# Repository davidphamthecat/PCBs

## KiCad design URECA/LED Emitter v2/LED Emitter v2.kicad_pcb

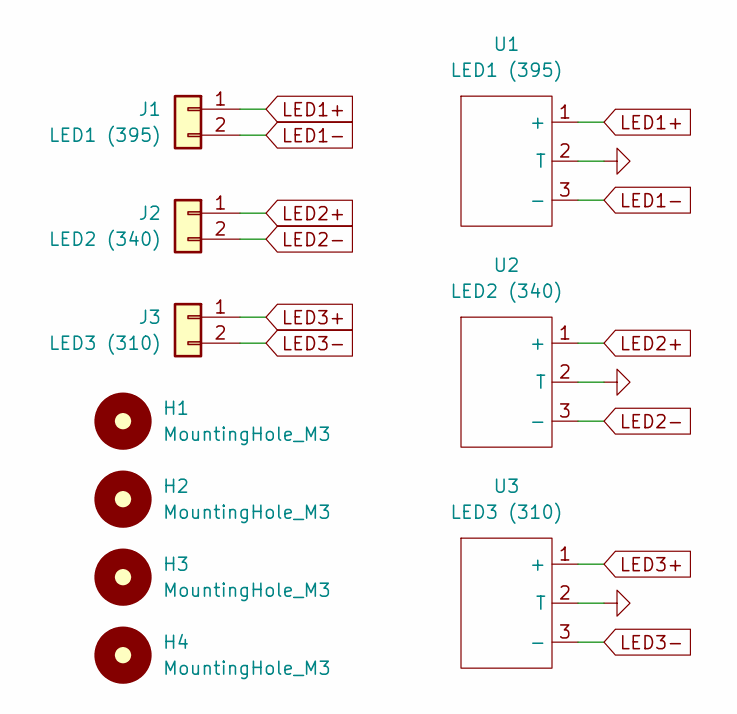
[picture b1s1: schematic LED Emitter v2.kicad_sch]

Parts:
H1, H2, H3, H4: MountingHole_M3; MountingHole_3.2mm_M3_DIN965_Pad_TopBottom; LCSC DNP
J1: LED1 (395); JST_XH_S2B-XH-A_1x02_P2.50mm_Horizontal
J2: LED2 (340); JST_XH_S2B-XH-A_1x02_P2.50mm_Horizontal
J3: LED3 (310); JST_XH_S2B-XH-A_1x02_P2.50mm_Horizontal
U1: LED1 (395); HOUKEM_LED
U2: LED2 (340); VS5252 LED
U3: LED3 (310); VS5252 LED

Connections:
GND: U1.2 (T), U2.2 (T), U3.2 (T)
LED1+: J1.1, U1.1 (+)
LED1-: J1.2, U1.3 (-)
LED2+: J2.1, U2.1 (+)
LED2-: J2.2, U2.3 (-)
LED3+: J3.1, U3.1 (+)
LED3-: J3.2, U3.3 (-)

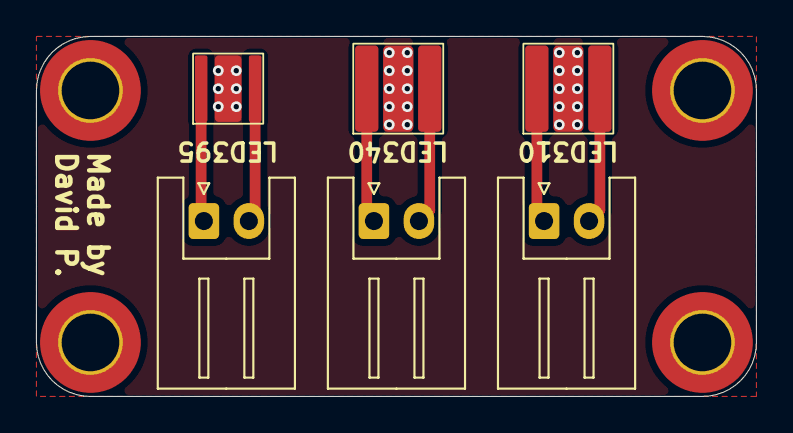
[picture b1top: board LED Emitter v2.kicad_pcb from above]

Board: 2 copper layers, 40.0 x 20.0 mm, 10 parts (0 on the bottom side), 7 nets.

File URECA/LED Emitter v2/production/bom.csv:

Designator,Footprint,Quantity,Value,LCSC Part #
"H1, H2, H3, H4",MountingHole_3.2mm_M3_DIN965_Pad_TopBottom,4,MountingHole_M3,DNP
J1,JST_XH_S2B-XH-A_1x02_P2.50mm_Horizontal,1,LED1 (395),
J2,JST_XH_S2B-XH-A_1x02_P2.50mm_Horizontal,1,LED2 (340),
J3,JST_XH_S2B-XH-A_1x02_P2.50mm_Horizontal,1,LED3 (310),
U1,HOUKEM_LED,1,LED1 (395),
U2,VS5252 LED,1,LED2 (340),
U3,VS5252 LED,1,LED3 (310),

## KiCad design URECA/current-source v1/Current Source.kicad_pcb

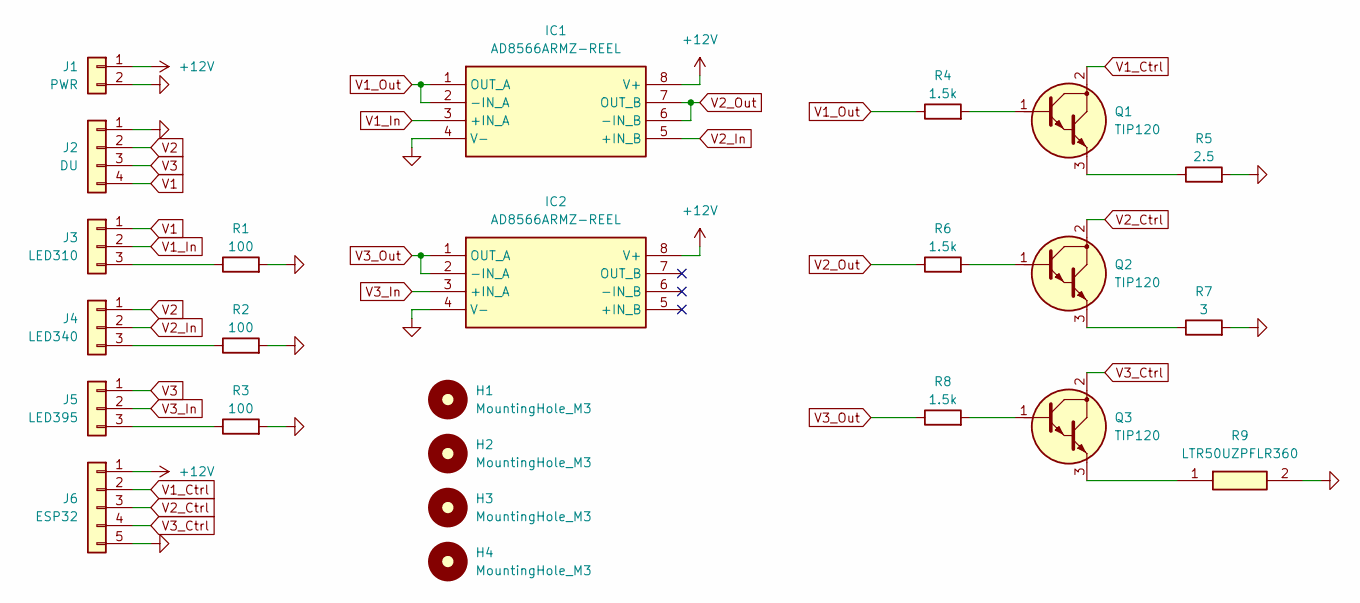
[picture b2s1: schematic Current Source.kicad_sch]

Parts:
H1, H2, H3, H4: MountingHole_M3; MountingHole_3.2mm_M3_DIN965_Pad_TopBottom; LCSC DNP
IC1, IC2: AD8566ARMZ-REEL; SOP65P490X110-8N; Mouser Part Number 584-AD8566ARMZ-R
J1: PWR; PinHeader_1x02_P1.00mm_Vertical
J2: DU; PinHeader_1x04_P1.00mm_Vertical
J3: LED310; PinHeader_1x03_P1.00mm_Vertical
J4: LED340; PinHeader_1x03_P1.00mm_Vertical
J5: LED395; PinHeader_1x03_P1.00mm_Vertical
J6: ESP32; PinHeader_1x05_P1.00mm_Vertical
Q1, Q2, Q3: TIP120; TO-220-3_Vertical_BCE
R1, R2, R3: 100; R_0805_2012Metric
R4, R6, R8: 1.5k; R_0805_2012Metric
R5: 2.5; R_1206_3216Metric
R7: 3; R_2010_5025Metric
R9: LTR50UZPFLR360; RESC2550X73N; Mouser Part Number 755-LTR50UZPFLR360

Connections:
+12V: IC1.8 (V+), IC2.8 (V+), J1.1, J6.1
GND: IC1.4 (V-), IC2.4 (V-), J1.2, J2.1, J6.5, R1.2, R2.2, R3.2, R5.2, R7.2, R9.2
unnamed: J3.3, R1.1
unnamed: J4.3, R2.1
unnamed: J5.3, R3.1
unnamed: Q1.1 (B), R4.2
unnamed: Q1.3 (E), R5.1
unnamed: Q2.1 (B), R6.2
unnamed: Q2.3 (E), R7.1
unnamed: Q3.1 (B), R8.2
unnamed: Q3.3 (E), R9.1
V1: J2.4, J3.1
V1_Ctrl: J6.2, Q1.2 (C)
V1_In: IC1.3 (+IN_A), J3.2
V1_Out: IC1.1 (OUT_A), IC1.2 (-IN_A), R4.1
V2: J2.2, J4.1
V2_Ctrl: J6.3, Q2.2 (C)
V2_In: IC1.5 (+IN_B), J4.2
V2_Out: IC1.6 (-IN_B), IC1.7 (OUT_B), R6.1
V3: J2.3, J5.1
V3_Ctrl: J6.4, Q3.2 (C)
V3_In: IC2.3 (+IN_A), J5.2
V3_Out: IC2.1 (OUT_A), IC2.2 (-IN_A), R8.1

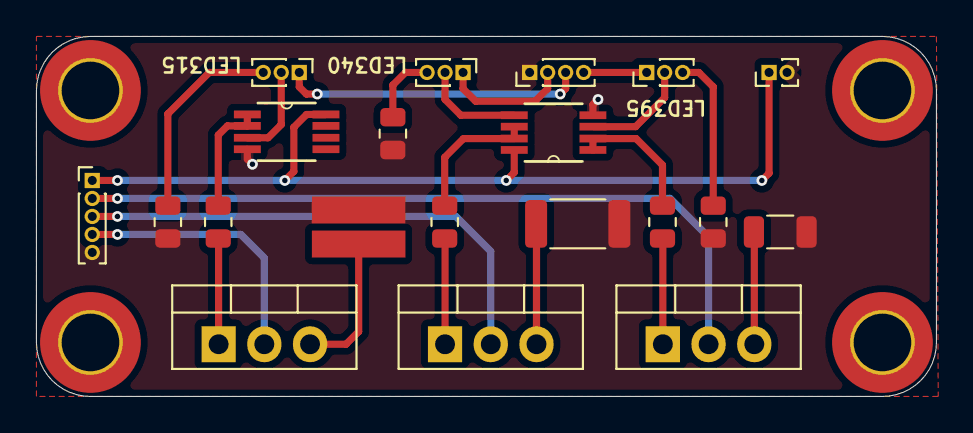
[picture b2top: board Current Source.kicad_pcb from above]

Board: 2 copper layers, 50.0 x 20.0 mm, 24 parts (0 on the bottom side), 23 nets.

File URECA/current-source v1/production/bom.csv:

Designator,Footprint,Quantity,Value,LCSC Part #
"H1, H2, H3, H4",MountingHole_3.2mm_M3_DIN965_Pad_TopBottom,4,MountingHole_M3,DNP
"IC1, IC2",SOP65P490X110-8N,2,AD8566ARMZ-REEL,
J1,PinHeader_1x02_P1.00mm_Vertical,1,PWR,
J2,PinHeader_1x04_P1.00mm_Vertical,1,DU,
J3,PinHeader_1x03_P1.00mm_Vertical,1,LED310,
J4,PinHeader_1x03_P1.00mm_Vertical,1,LED340,
J5,PinHeader_1x03_P1.00mm_Vertical,1,LED395,
J6,PinHeader_1x05_P1.00mm_Vertical,1,ESP32,
"Q1, Q2, Q3",TO-220-3_Vertical_BCE,3,TIP120,
"R1, R2, R3",0805,3,100,
"R4, R6, R8",0805,3,1.5k,
R5,1206,1,2.5,
R7,2010,1,3,
R9,RESC2550X73N,1,LTR50UZPFLR360,

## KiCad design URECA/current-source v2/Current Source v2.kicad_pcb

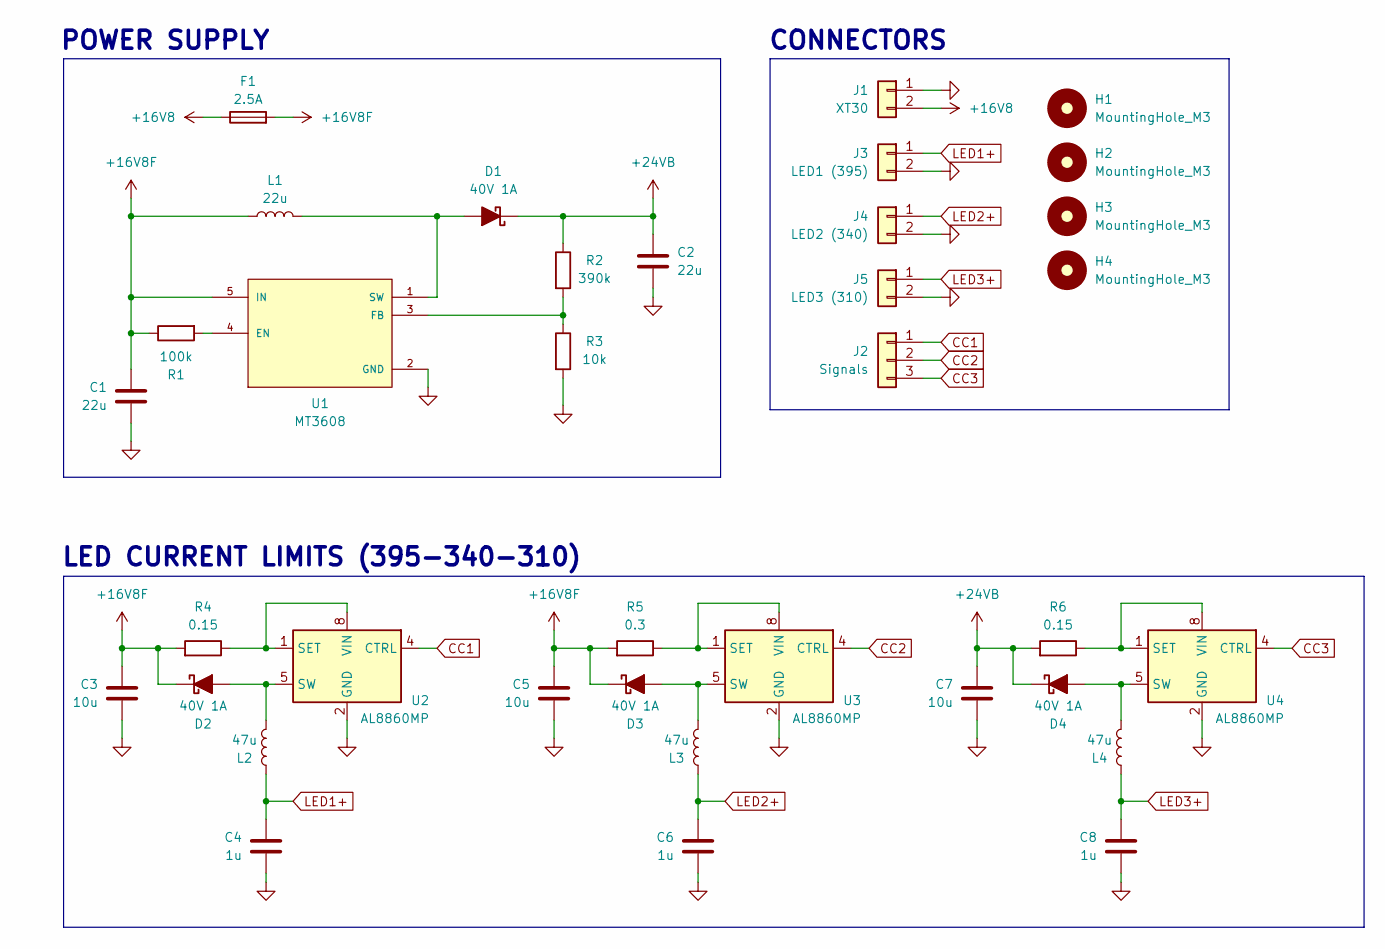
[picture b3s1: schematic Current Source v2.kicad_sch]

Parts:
C1, C2: 22u; C_0805_2012Metric
C3, C5, C7: 10u; C_0805_2012Metric
C4, C6, C8: 1u; C_0805_2012Metric
D1, D2, D3, D4: 40V 1A; D_SMA
F1: 2.5A; Fuse_1206_3216Metric
H1, H2, H3, H4: MountingHole_M3; MountingHole_3.2mm_M3_DIN965_Pad_TopBottom; LCSC DNP
J1: XT30; AMASS_XT30U-M_1x02_P5.0mm_Vertical
J2: Signals; PinHeader_1x03_P1.00mm_Vertical
J3: LED1 (395); JST_XH_B2B-XH-A_1x02_P2.50mm_Vertical
J4: LED2 (340); JST_XH_B2B-XH-A_1x02_P2.50mm_Vertical
J5: LED3 (310); JST_XH_B2B-XH-A_1x02_P2.50mm_Vertical
L1: 22u; IND_MSS7341-223MLD
L2, L3, L4: 47u; 46473C
R1: 100k; R_0805_2012Metric
R2: 390k; R_0805_2012Metric
R3: 10k; R_0805_2012Metric
R4, R6: 0.15; R_1206_3216Metric
R5: 0.3; R_1206_3216Metric
U1: MT3608; SOT95P280X145-6N; PARTREV 1.0
U2, U3, U4: AL8860MP; MSOP-8-1EP_3x3mm_P0.65mm_EP1.5x1.8mm

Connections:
+16V8: F1.1, J1.2
+16V8F: C1.1, C3.1, C5.1, D2.1 (K), D3.1 (K), F1.2, L1.1, R1.1, R4.2, R5.2, U1.5 (IN)
+24VB: C2.1, C7.1, D1.1 (K), D4.1 (K), R2.1, R6.2
CC1: J2.1, U2.4 (CTRL)
CC2: J2.2, U3.4 (CTRL)
CC3: J2.3, U4.4 (CTRL)
GND: C1.2, C2.2, C3.2, C4.2, C5.2, C6.2, C7.2, C8.2, J1.1, J3.2, J4.2, J5.2, R3.2, U1.2 (GND), U2.2 (GND), U2.3 (GND), U2.9 (GND), U3.2 (GND), U3.3 (GND), U3.9 (GND), U4.2 (GND), U4.3 (GND), U4.9 (GND)
LED1+: C4.1, J3.1, L2.1
LED2+: C6.1, J4.1, L3.1
LED3+: C8.1, J5.1, L4.1
unnamed: D1.2 (A), L1.2, U1.1 (SW)
unnamed: D2.2 (A), L2.2, U2.5 (SW), U2.6 (SW)
unnamed: D3.2 (A), L3.2, U3.5 (SW), U3.6 (SW)
unnamed: D4.2 (A), L4.2, U4.5 (SW), U4.6 (SW)
unnamed: R1.2, U1.4 (EN)
unnamed: R2.2, R3.1, U1.3 (FB)
unnamed: R4.1, U2.1 (SET), U2.8 (VIN)
unnamed: R5.1, U3.1 (SET), U3.8 (VIN)
unnamed: R6.1, U4.1 (SET), U4.8 (VIN)

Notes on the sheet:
LED CURRENT LIMITS (395-340-310)
CONNECTORS
POWER SUPPLY

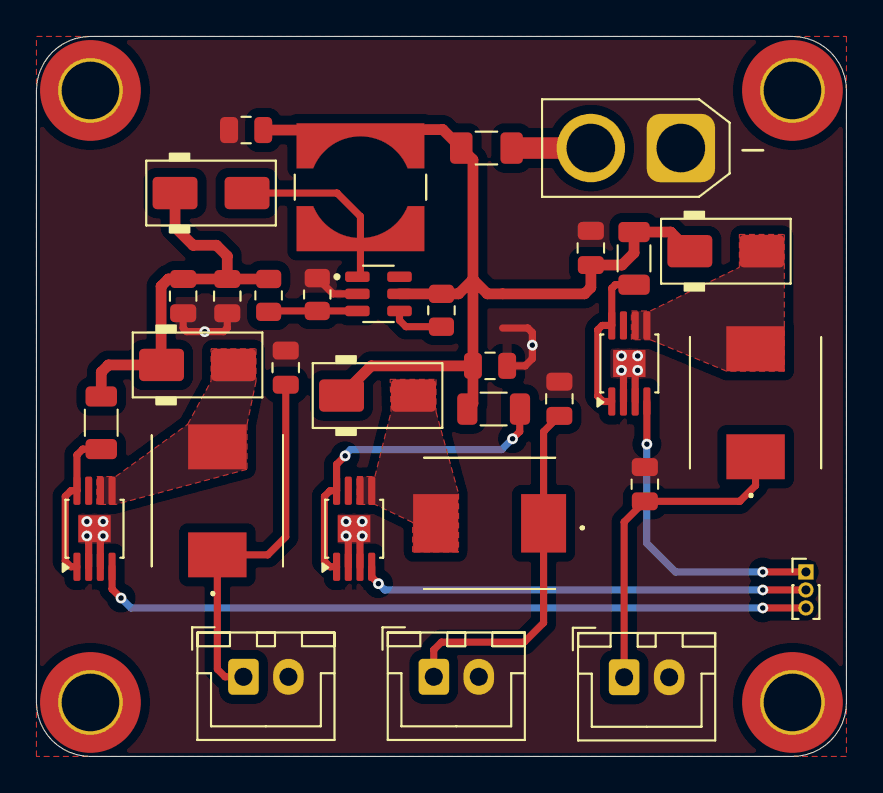
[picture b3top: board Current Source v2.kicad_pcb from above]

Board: 2 copper layers, 45.0 x 40.0 mm, 36 parts (0 on the bottom side), 19 nets.

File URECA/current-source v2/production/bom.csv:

Designator,Footprint,Quantity,Value,LCSC Part #
"C1, C2",0805,2,22u,
"C3, C5, C7",0805,3,10u,
"C4, C6, C8",0805,3,1u,
"D1, D2, D3, D4",D_SMA,4,40V 1A,
F1,1206,1,2.5A,
"H1, H2, H3, H4",MountingHole_3.2mm_M3_DIN965_Pad_TopBottom,4,MountingHole_M3,DNP
J1,AMASS_XT30U-M_1x02_P5.0mm_Vertical,1,XT30,
J2,PinHeader_1x03_P1.00mm_Vertical,1,Signals,
J3,JST_XH_B2B-XH-A_1x02_P2.50mm_Vertical,1,LED1 (395),
J4,JST_XH_B2B-XH-A_1x02_P2.50mm_Vertical,1,LED2 (340),
J5,JST_XH_B2B-XH-A_1x02_P2.50mm_Vertical,1,LED3 (310),
L1,IND_MSS7341-223MLD,1,22u,
"L2, L3, L4",46473C,3,47u,
R1,0805,1,100k,
R2,0805,1,390k,
R3,0805,1,10k,
"R4, R6",1206,2,0.15,
R5,1206,1,0.3,
U1,SOT95P280X145-6N,1,MT3608,
"U2, U3, U4",MSOP-8-1EP_3x3mm_P0.65mm_EP1.5x1.8mm,3,AL8860MP,
